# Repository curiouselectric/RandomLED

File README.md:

# RandomLED
A DIY kit to make a solar powered Dice or 8-Ball Unit

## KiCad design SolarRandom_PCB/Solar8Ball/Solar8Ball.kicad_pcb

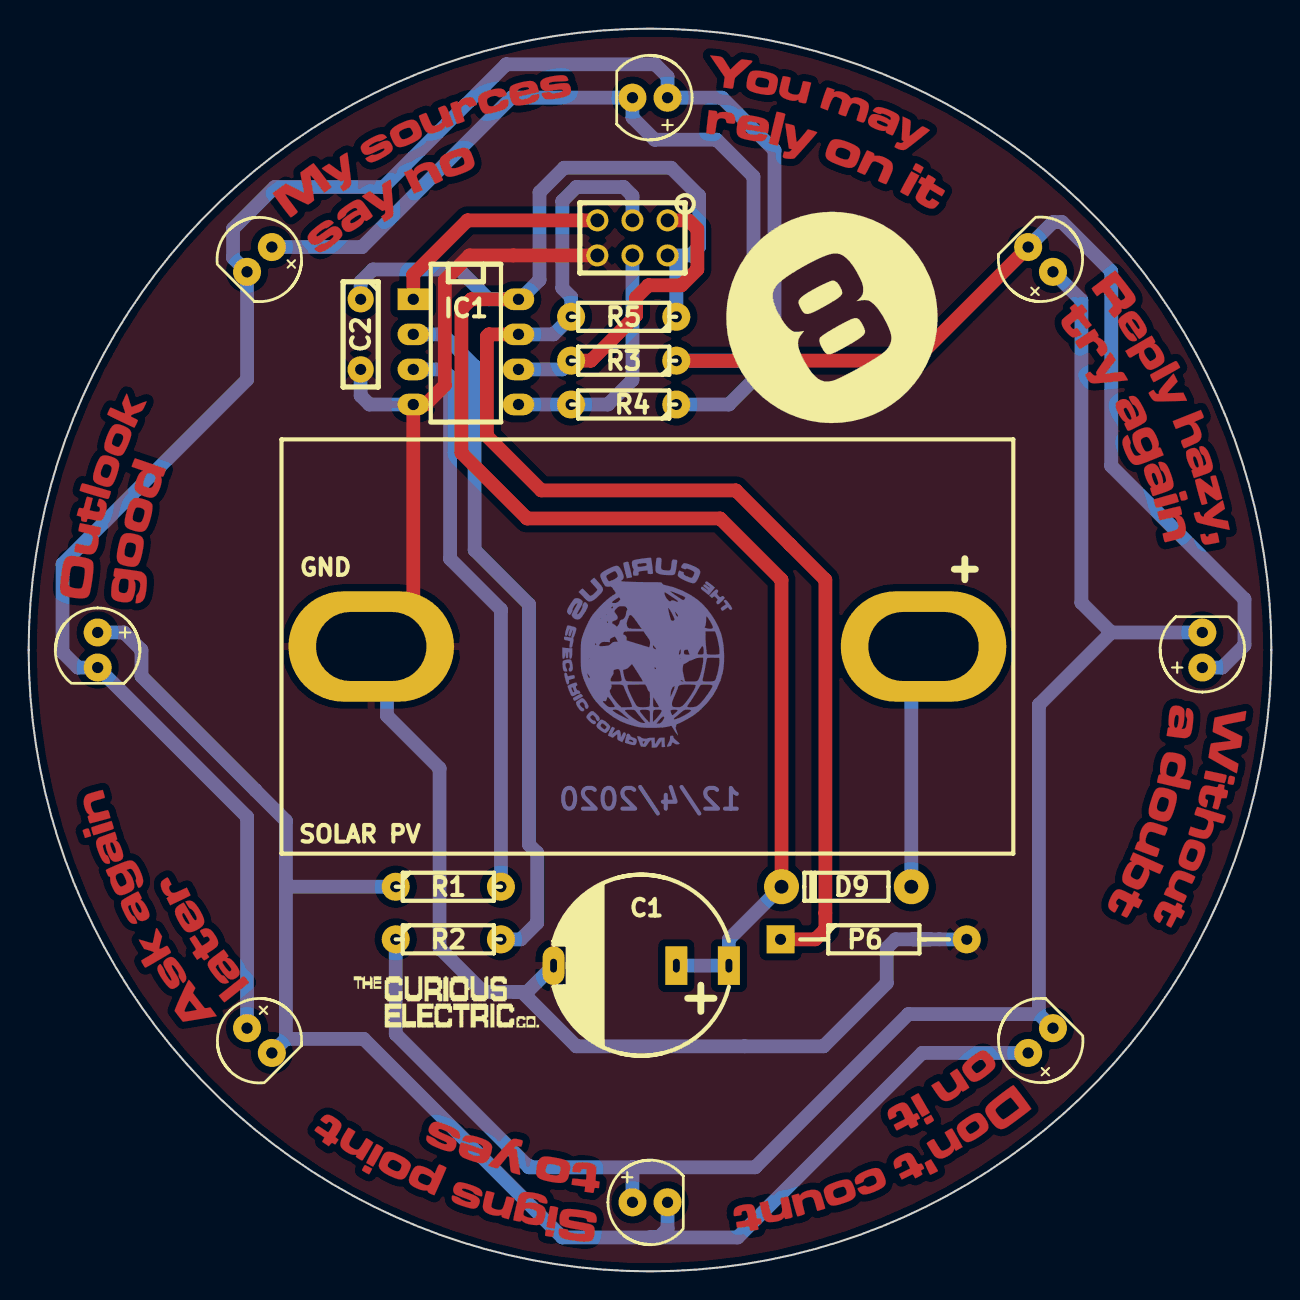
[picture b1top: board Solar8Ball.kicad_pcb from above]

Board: 2 copper layers, 90.0 x 90.0 mm, 24 parts (0 on the bottom side), 13 nets.

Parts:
C1: 0.47F; C_0_47F_SuperCap_2POS
C2: 100n; C1_wide_lg_pad_2
D1, D2, D3, D4, D5, D6, D7, D8: LED; LED-5MM_larg_pad
D9: 1N5819; TH_Diode_1
IC1: ATTINY85-P; DIP-8_300_ELL
P1: PCB_TEXT; Solar8Ball_Word_Mask3
P2: ISP; ISP_3x2
P4: HOLES; PCB_Circle_100mm_BSS
P5: LOGO1; 2020_04_14_CuriousElectricCompany_Logo_Round_15mm_BCu
P6: SWITCH; TH_SW_SW200D
P7: LOGO2; TCEC_Words_13mm
R1, R2, R3, R4: 120; R3-LARGE_PADS_0_8_hole
R5: 100k; R3-LARGE_PADS_0_8_hole
SC1: SOLAR PV; PV_53x30mm_Area

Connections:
/LED0: IC1.3, R1.2
/LED1: IC1.2, R2.2
/LED2: IC1.6, P2.1, R3.2
/LED3: IC1.5, P2.4, R4.2
/SWITCH: IC1.7, P2.3, P6.1, R5.2
GND: C1.2, C2.2, IC1.4, P2.6, P6.2, SC1.2
unnamed: D1.1, D2.2, D3.2, D4.1, R2.1
unnamed: D1.2, D2.1, D7.1, D8.2, R1.1
unnamed: D3.1, D4.2, D5.2, D6.1, R3.1
unnamed: D5.1, D6.2, D7.2, D8.1, R4.1
unnamed: D9.2, SC1.1
unnamed: IC1.1, P2.5
VCC: C1.1, C2.1, D9.1, IC1.8, P2.2, R5.1

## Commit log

2020-04-09 Initial Commit of PCB and firmware
2020-04-09 removed old files
2020-04-09 Updated PCBs
2020-05-14 Updated Software and PCB design
2020-05-14 Removed old code
2020-05-15 Added Solar 8 Ball Instructions
2020-05-15 Updates of both sets of instructions
2020-05-22 PCB and instructions
2022-07-15 updated ins tructions
